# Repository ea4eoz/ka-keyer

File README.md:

# KA-Keyer
## A simple keyer for the high speed CW operators

KA-Keyer is a simple keyer with an emphasis on high-speed operation. It can be considered a derivative from the Open CW Keyer MK2, an Arduino-based CW keyer from OK1CDJ.

This is the second keyer release, and the Arduino Nano board has been replaced by a Waveshare RP2040 Zero board (or compatible clone). Anyway the current firmware can be flashed on both keyers, the old ones based on Arduino Nano and the new ones based on the RP2040 chip with identical features.

## Features

- No bells and whistles. Just an almost dumb keyer you can use with or without a computer. If you need / want keying commands, memories, automatic serial numbers, and so on, this is not the keyer you want.

- Plain Iambic, Iambic A, Iambic B or Ultimate mode keying with corresponding dot/dash memories.

- Adjustable keying speed from 10 up to 99 WPM

- Adjustable dot weight between 25% and 75%

- Adjustable dit-dash ratio from 2.0 to 4.0

- Partial compatibility with WinKeyer, tested with N1MM, Fldigi, Rumlog...

- USB-C connector

## New in version 2.2

- EEPROM leveling, to prevent premature EEPROM wearing.

- On screen CW decoder, useful to practice yourself and check your manipulation.

- General code optimizations and rewrite in a more C-like way.

## Usage

The user interface is quite simple. A short press on the rotary button changes between menu entries and the rotary action changes the value of the selected menu. There are two sets of menus: The most often used and the less often used.

The first set of menus contains the most used options:

__Speed__: The CW speed, using the PARIS method, where the dot length is calculated, in milliseconds, as 1200 divided by the desired speed.

__Weight__: The dot weight, defined as the percentage of time the dot last inside its own timeslot. Normal CW uses a 50% dot weight.

__Ratio__: The length of a dash in PARIS units. Normal CW uses a dash three times longer than the dot.

The second set of menus contais some less used adjustments:

__Decoder__: Enables or disables screen decoder. It can be configured to show uppercase or lowercase letters.

__Sidetone__: Enables or disables the built-in buzzer

__Sidetone__ __frequency__: Adjust the sidetone's audio frecuency, from 400 to 1500 Hz.

__Keyer__: Determines the type of keyer. It implements plain Iambic, Iambic A, Iambic B and Ultimate.

__Paddles__: to configure normal (point on left) or reverse paddles (point on right).

You can change between the two menu sets with a long press on the rotary button.

KA-Keyer has some level of compatibility with WinKeyer, so you can use it with logging and contest programs, like Fldigi, N1MM, RumLog, etc. Don't expect a support for every Winkeyer feature, but just the bare minimum as this function seems to be phased out in favour of transceiver's CAT keying.

## Compiling and flashing for the Arduino Nano based KA-Keyer

The old Arduino Nano based KA_Keyer will be supportted as long as the Atmega328p can withstand the new features and fixes.

To upgrade it with this version, first remove the jumper marked PRG at the back panel and connect it to your computer.

The firmware uses no external libraries so it should be very easy to make it to compile. For a sucessful flashing, after loading the ka-keyer.ino file, you must set up the arduino IDE in this way:

Menu ---> Tools ---> Board ---> Arduino AVR Boards ---> Arduino Nano

Menu ---> Tools ---> Processor ---> ATmega328p (Old bootloader) (*)

Menu ---> Tools ---> Port ---> Select the serial port your KA-Keyer is attached to.

After this, using Menu ---> Sketch ---> Upload (or Ctrl-U) should flash your keyer with KA-Keyer firmware without problems. If flashing was sucessful you should hear the leter __K__ while the screen shows the actual firmware version.

(*) While most of the Arduinos Nano I had came with the old bootloader, lately a few of them came with the new one, so if you get errors trying to flash your unit, try Menu ---> Tools ---> Processor ---> ATmega328p

Remember to put in back the jumper at the rear of the keyer after flashing it to prevent accidental flashing and / or keyer resets because the computer's OS polling the serial ports.

Many programs can't use the keyer without the jumper because it resets itself everytime the program opens the serial port (the jumper prevent this). If this is happening, you will hear a __K__ everytime the program is trying to connect with the keyer because it is resetting itself.

## Compiling and flashing for the Waveshare RP2040 Zero based KA-Keyer

First, make sure you have configured support for the RP2040 microcontroller in Arduino IDE.

Go to Menu ---> Preferences, and make sure you have the following URL added in the Aditional boards manager URLs box:

https://github.com/earlephilhower/arduino-pico/releases/download/global/package_rp2040_index.json

If not, after adding it the Arduino IDE will download all the required files to support the RP2040 microntroller.

Once the support for the RP2040 is installed, use your favorite text editor and edit this file:

.arduino15/packages/rp2040/hardware/rp2040/[VERSION]/cores/rp2040/SerialUSB.cpp

.arduino15 is a hidden directory in your home directory in Linux / Mac systems. On windows systems SerialUSB.cpp is located at:

C:\Users\{username}\AppData\Local\Arduino15\packages/rp2040/hardware/rp2040/[VERSION]/cores/rp2040/SerialUSB.cpp

[VERSION] is the current Raspberry Pi Pico SDK version installed, as the time of writting this 4.5.3

Once you have open the SerialUSB.cpp file in your editor look for the CheckSerialReset() function and empty it, for example:

    static void CheckSerialReset() {
        if (!_rebooting && (_bps == 1200) && (!_dtr)) {
    //      if (__isFreeRTOS) {
    //          __freertos_idle_other_core();
    //      }
    //      _rebooting = true;
    //      // Disable NVIC IRQ, so that we don't get bothered anymore
    //      irq_set_enabled(USBCTRL_IRQ, false);
    //      // Reset the whole USB hardware block
    //      reset_block(RESETS_RESET_USBCTRL_BITS);
    //      unreset_block(RESETS_RESET_USBCTRL_BITS);
    //      // Delay a bit, so the PC can figure out that we have disconnected.
    //      busy_wait_ms(3);
    //      reset_usb_boot(0, 0);
    //      while (1); // WDT will fire here
        }
    }

This is needed because the Waveshare RP2040 Zero, and many other boards with native USB support uses opening the serial port at 1200 bauds to reset and launch the bootloader. Any program supporting Winkeyer will open the serial port at 1200 bauds, so the board will reset and enters in the flashing mode, preventing the usage as a CW keyer.

Once you have empty the CheckSerialReset() function, you can select the board as Waveshare RP2040 Zero and flash it. The first time you can use the serial port to flash it, but next uploads must be done using the BOOT button and UF2 method.

Once you have programmed your board, you can restore the CheckSerialReset() function.

KA-keyer has been developed and tested using Arduino IDE version 2.3.5 but any other version should work just fine.

## Mounting a RP2040 based KA-Keyer

Some tips for mount the RP2040 based keyer:

### Mounting the OLED screen

Mounting the OLED screen is the most dificult part. First, you will need a small piece of PCB board, about 28 x 14 mm with at least one side of copper. You must solder it vertically to the main PCB using the tinned area as ahown in the next photos.

Now take the oled and separate the display glass from the small PCB. I use a small piece of dental floss carefully passing it between the glass and the PCB. Once the glass is free clean the adhesive using isopropyl alcohol.

Now using a piece of double-sided adhesive foam, put the OLED glass into the piece of PCB board you soldered earlier. For a good aling, put the end of the display area aligned with the upper side of the main PCB.

Now you can solder the OLED PCB to the main PCB, but first take note of the pinout of the OLED.

SSD1306 based oled display come with two different pinouts: GND-VCC-SCL-SDA, or VCC-GND-SCL-SDA, and in 5 volt or 3.3 volt versions. You can use all of them with KA-Keyer. There are two solder jumpers next to the OLED pins. Just place a small solder blob in each jumper according to the signal for that pin. G for GND or V for Vcc.

Most OLED modules displays work at 5 volts. They are easily identificables because in the OLED PCB you can find a voltage regulator, usually a small SOT-23 one marked 662K. If your OLED has this regulator, just put a solder blob on the 5V jumper and do not populate U6.

If your OLED module do not have any voltage regulator it is a 3.3 volts one. In this case populate U6 with a XC6206P332MR (SMD marking: 662K) SOT-23 voltage regulator and do not put any solder blob on the 5V jumper.

### Mounting the Waveshare RP2040 Zero board

The Waveshare RP2040 Zero board is a double side board with components at both sides, and there are some components under the board in the KA-Keyer main PCB so you need to solder it in a elevated form. Just put a pair of plastic insulators from a pin header as shown in the next photo and solder it to the board.

### Power bank operation

R15 and R16 are two 120 ohms 0.25 watts resistors that increases the current draw of the keyer in about 80 mA. This should be enough to keep a small power bank alive while using it with KA-Keyer. They are optional and you can omit them if you do not have plans to use a power bank with KA-Keyer.

## Materials

### Aluminum box

The box used is the same used by the Open CW Keyer MK2, that can be find on sites like eBay, Aliexpress, etc. It is one announced as Extruded DIY Enclosure Aluminum Box with dimensions of 1.97 x 2.28 x 0.94 inches or 50 x 58 x 24 millimeters

### Rotary encoder

It is announced as a generic horizontal rotary EC11 encoder in sites like eBay, Aliexpress, ect. The one used is the one with 15mm handle. Use plum or half handle as you like.

## Links

The Open CW Keyer MK2 project repository:
[https://github.com/ok1cdj/OpenCWKeyerMK2](https://github.com/ok1cdj/OpenCWKeyerMK2)

Rotary encoder in Aliexpress:
[https://aliexpress.com/item/1005006128388016.html](https://aliexpress.com/item/1005006128388016.html)

Aluminum box in Aliexpress:
[https://aliexpress.com/item/1005008145475053.html](https://aliexpress.com/item/1005008145475053.html)

## License

The source files of the KA-Keyer in this repository are made available under the GPLv3 license.

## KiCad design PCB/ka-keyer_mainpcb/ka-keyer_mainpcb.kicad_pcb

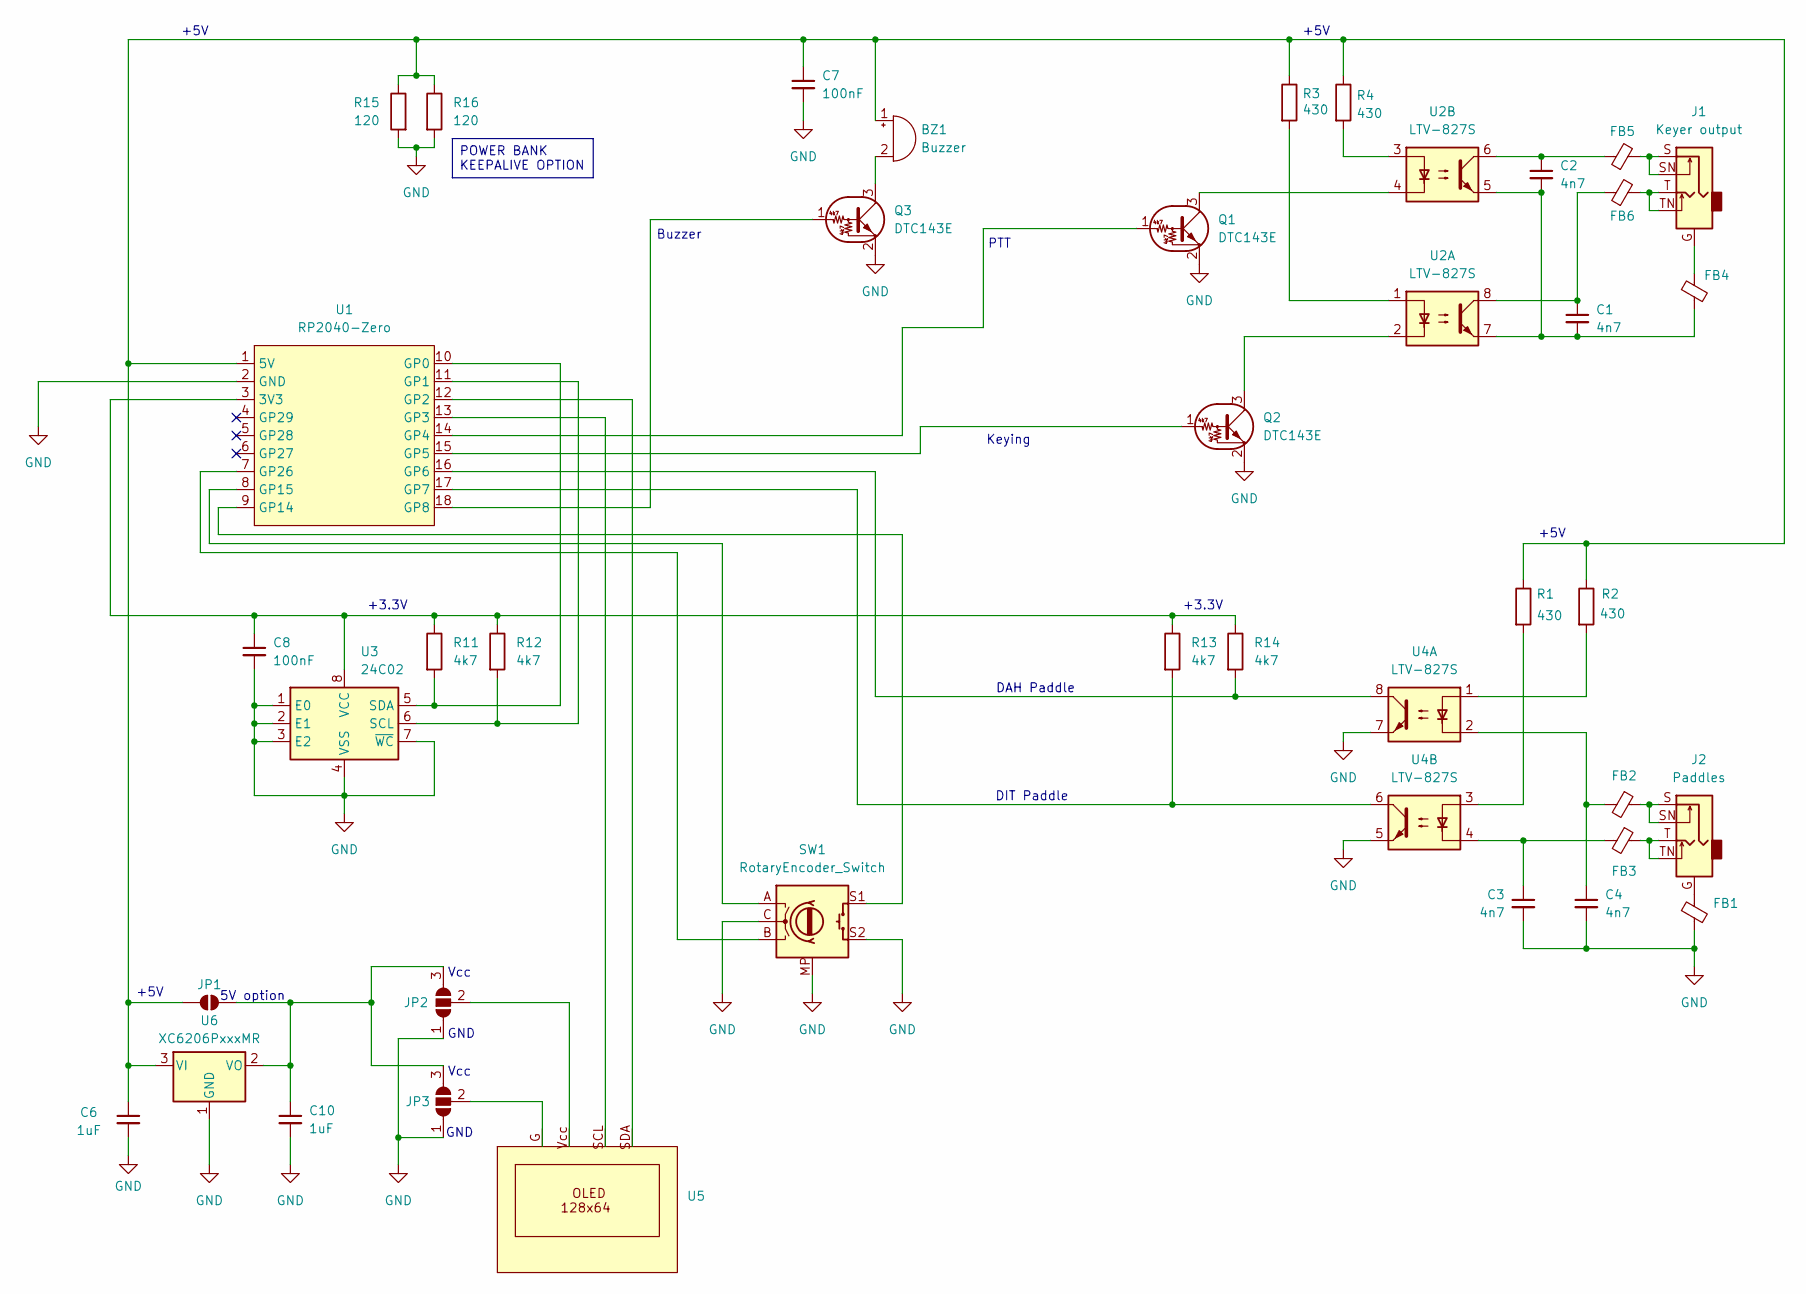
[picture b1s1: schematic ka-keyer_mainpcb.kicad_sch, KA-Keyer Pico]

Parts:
BZ1: Buzzer; Buzzer_12x9.5RM7.6
C1, C2, C3, C4: 4n7; C_0805_2012Metric_Pad1.18x1.45mm_HandSolder
C6, C10: 1uF; C_0805_2012Metric_Pad1.18x1.45mm_HandSolder
C7, C8: 100nF; C_0805_2012Metric_Pad1.18x1.45mm_HandSolder
FB1, FB2, FB3, FB4, FB5, FB6: C_0805_2012Metric_Pad1.18x1.45mm_HandSolder
J1: Keyer output; AUDIO-JACK
J2: Paddles; AUDIO-JACK
JP1: SolderJumper_2_Open; SolderJumper-2_P1.3mm_Open_RoundedPad1.0x1.5mm
JP2, JP3: SolderJumper-3_P1.3mm_Open_RoundedPad1.0x1.5mm
Q1, Q2, Q3: DTC143E; SOT-23-3
R1, R2, R3, R4: 430; R_0805_2012Metric_Pad1.20x1.40mm_HandSolder
R11, R12, R13, R14: 4k7; R_0805_2012Metric_Pad1.20x1.40mm_HandSolder
R15, R16: 120; R_Axial_DIN0207_L6.3mm_D2.5mm_P10.16mm_Horizontal
SW1: RotaryEncoder_Switch; Aliexpress horizontal encoder
U1: RP2040-Zero; RP2040 Zero DIL
U2, U4: LTV-827S; SMDIP-8_W9.53mm
U3: 24C02; SOIC-8_3.9x4.9mm_P1.27mm
U5: OLED-128x64
U6: XC6206PxxxMR; SOT-23-3

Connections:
GND: C3.2, C4.2, C6.2, C7.2, C8.2, C10.2, FB1.2, JP2.1 (A), JP3.1 (A), Q1.2 (E), Q2.2 (E), Q3.2 (E), R15.2, R16.2, SW1.C, SW1.MP, SW1.S2, U1.2 (GND), U3.1 (E0), U3.2 (E1), U3.3 (E2), U3.4 (VSS), U3.7 (~WC), U4.5, U4.7, U6.1 (GND)
unnamed: BZ1.1 (+), C6.1, C7.1, JP1.1 (A), R1.1, R2.1, R3.1, R4.1, R15.1, R16.1, U1.1 (5V), U6.3 (VI)
unnamed: BZ1.2 (-), Q3.3 (C)
unnamed: C1.1, FB6.1, U2.8
unnamed: C1.2, C2.2, FB4.2, U2.5, U2.7
unnamed: C2.1, FB5.1, U2.6
unnamed: C3.1, FB3.2, U4.4
unnamed: C4.1, FB2.2, U4.2
unnamed: FB1.1, J2.G
unnamed: FB2.1, J2.S, J2.SN
unnamed: FB3.1, J2.T, J2.TN
unnamed: FB4.1, J1.G
unnamed: FB5.2, J1.S, J1.SN
unnamed: FB6.2, J1.T, J1.TN
unnamed: C10.1, JP1.2 (B), JP2.3 (B), JP3.3 (B), U6.2 (VO)
unnamed: JP2.2 (C), U5.Vcc
unnamed: JP3.2 (C), U5.G
unnamed: Q1.1 (B), U1.14 (GP4)
unnamed: Q1.3 (C), U2.4
unnamed: Q2.1 (B), U1.15 (GP5)
unnamed: Q2.3 (C), U2.2
unnamed: Q3.1 (B), U1.18 (GP8)
unnamed: R1.2, U4.3
unnamed: R2.2, U4.1
unnamed: R3.2, U2.1
unnamed: R4.2, U2.3
unnamed: C8.1, R11.1, R12.1, R13.1, R14.1, U1.3 (3V3), U3.8 (VCC)
unnamed: R11.2, U1.10 (GP0), U3.5 (SDA)
unnamed: R12.2, U1.11 (GP1), U3.6 (SCL)
unnamed: U1.12 (GP2), U5.SDA
unnamed: U1.13 (GP3), U5.SCL
unnamed: R14.2, U1.16 (GP6), U4.8
unnamed: R13.2, U1.17 (GP7), U4.6
unnamed: SW1.S1, U1.9 (GP14)
unnamed: SW1.A, U1.8 (GP15)
unnamed: SW1.B, U1.7 (GP26)

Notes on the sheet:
DAH Paddle
DIT Paddle
Vcc
+3.3V
GND
+5V
Keying
PTT
5V option
Buzzer
POWER BANK KEEPALIVE OPTION

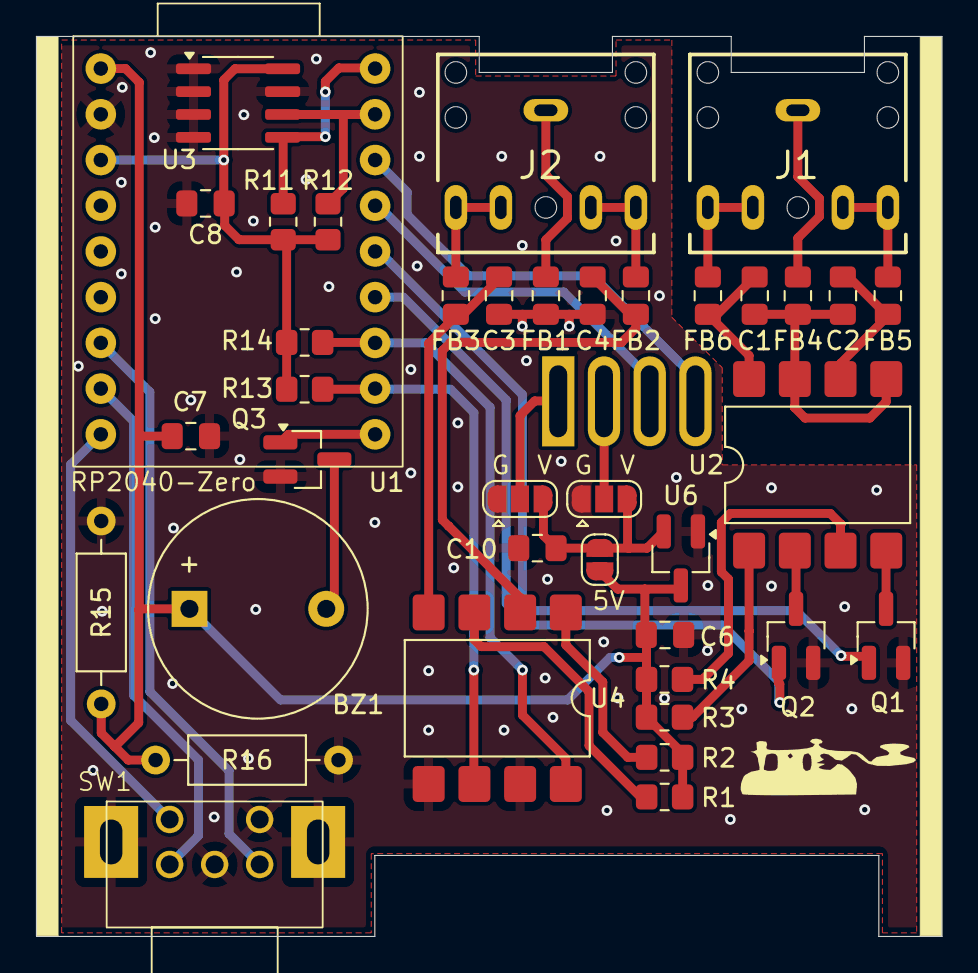
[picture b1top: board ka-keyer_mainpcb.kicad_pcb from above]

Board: 2 copper layers, 50.3 x 50.0 mm, 40 parts (1 on the bottom side), 36 nets.

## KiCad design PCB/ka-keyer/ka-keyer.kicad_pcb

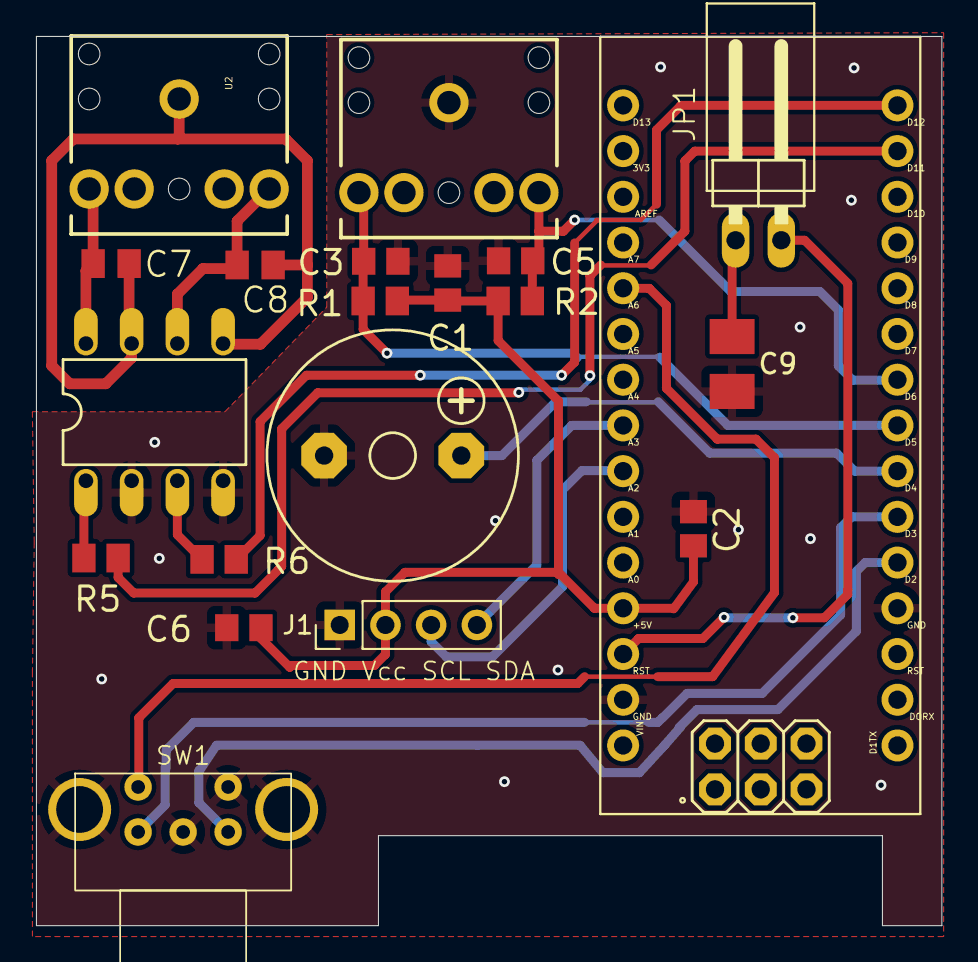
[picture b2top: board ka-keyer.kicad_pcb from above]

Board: 2 copper layers, 50.3 x 49.4 mm, 20 parts (0 on the bottom side), 19 nets.

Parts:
C1, C2, C3, C5, C6: C-EUC0805; C0805
C7, C8: C-EUC0805K; C0805K
C9: CPOL-EUB/3528-21R; B_3528-21R
J1: 128x64 OLED; PinHeader_1x04_P2.54mm_Vertical
JP1: PINHD-1X2/90; 1X02_90
OK1: TLP627; DIL08
PCB1: ARDUINO_NANO
R1, R2, R5, R6: R-EU_M0805; M0805
SG1: BUZZER; F_CM12P
SW1: RotaryEncoder_Switch_MP; Aliexpress horizontal encoder
U1, U2: AUDIO-JACKPTH; AUDIO-JACK

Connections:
GND: C1.2, C2.2, C3.2, C5.2, C6.2, C9.-, J1.1, OK1.2 (C), OK1.4 (C), PCB1.GND, PCB1.GND., SG1.- (2), SW1.C, SW1.MP, SW1.S2, U1.SLEEVE
unnamed: C9.+, JP1.1
unnamed: C1.1, C2.1, C6.1, J1.2, PCB1.5V, R1.2, R2.2
unnamed: J1.3, PCB1.A5
unnamed: J1.4, PCB1.A4
unnamed: JP1.2, PCB1.RST.
unnamed: OK1.1 (A), R5.1
unnamed: C7.2, OK1.8 (COL), U2.TIP (LEFT)
unnamed: C7.1, C8.1, OK1.5 (EMIT), OK1.7 (EMIT), U2.SLEEVE
unnamed: OK1.3 (A), R6.1
unnamed: C8.2, OK1.6 (COL), U2.RING (RIGHT)
unnamed: PCB1.A1, SW1.S1
unnamed: PCB1.D2, SW1.B
unnamed: PCB1.D3, SW1.A
unnamed: PCB1.D11, R5.2
unnamed: PCB1.D12, R6.2
unnamed: PCB1.D4, SG1.+ (1)
unnamed: C3.1, PCB1.D5, R1.1, U1.TIP (LEFT)
unnamed: C5.1, PCB1.D6, R2.1, U1.RING (RIGHT)

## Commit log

2024-04-01 Added description
2024-05-12 Formating test
2024-05-13 First release
2024-05-13 Fix some typos
2024-05-14 Fixing some more typos
2024-05-14 Little tweak in task_serialout
2024-05-16 Removed unnecessary buffer and task
2024-07-28 Version 2.0
2024-07-28 new schematic
2025-05-26 Version 2.2
2025-05-26 Added keyer logo images
2025-06-01 Updating documentation
